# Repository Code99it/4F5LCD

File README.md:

# Installation und Nutzung  
# Installation and Usage  

**Dieses Projekt ersetzt bei Fahrzeugen der VAG-Gruppe mit Plattform 4F (C6) das kleine Display in der Mitte des Kombiinstruments durch eine spezielle Mikrocontroller-Lösung. Die Bedienung erfolgt über die linken Tasten am Lenkrad:**  
- Drehen am Rad wählt einen Listeneintrag.  
- Klicken auf das Drehrad aktiviert den gewählten Eintrag.  
- Die MODE-Taste am Lenkrad wechselt zwischen den Menüseiten.  
- Die Auf-Ab-Taste am Wischerhebel und die Bestätigungstaste auf der Hebel-Unterseite sind zunächst wirkungslos, die Funktion wird ggf. in späteren Projektversionen noch einmal aufgegriffen.

**This project replaces the small display in the center of the instrument cluster with a custom microcontroller solution for vehicles of the VAG group using platform 4F (C6). Operation is via the left steering wheel controls:**  
- Rotating the knob selects a list item.  
- Pressing the knob activates the selected item.  
- The MODE button on the steering wheel switches between menu pages.  
- The up/down button on the wiper stalk and the confirm button on the underside of the stalk are initially non-functional; this feature may be revisited in a future project version.

## Was dir dieses Projekt nützt  
## What This Project Does for You  

- Du erhältst schnellen, sicheren Zugriff auf fahrzeuginterne Statusdaten, um Temperatur-, Drehzahl- oder Komfortparameter zu überwachen.  
- You get fast, secure access to in-vehicle status data to monitor temperature, RPM, or comfort parameters.  

## 1. Systemzugriff einrichten  
## 1. Set Up System Access  

- Dieses System greift ausschließlich lesend auf die fahrzeuginternen Bussysteme (z. B. CAN-Bus) zu.  
- Es werden nur Statusinformationen wie Temperatur, Drehzahl oder Komfortdaten erfasst.  
- Kein Zugriff auf sicherheitskritische Systeme (Bremsen, Airbags, ESP, ABS, Antrieb).  
- Eine Beeinflussung, Veränderung oder Steuerung dieser Systeme ist weder vorgesehen noch implementiert.  

- No access to safety-critical systems (brakes, airbags, ESP, ABS, drivetrain).  
- Only status information such as temperature, RPM or comfort data is collected.  
- This system uses read-only access to the vehicle’s internal bus systems (e.g. CAN bus).  
- Any manipulation, alteration or control of these systems is neither intended nor implemented.  

## 2. Infotainment-Funktionen aktivieren  
## 2. Enable Infotainment Functions  

- Für Menüauswahl und Displayanzeige wird schreibender Zugriff auf nicht sicherheitsrelevante Steuergeräte verwendet.  
- Dieser Zugriff ist funktional begrenzt und beeinflusst weder Fahrverhalten noch Fahrsicherheit.  

- Write access to non-safety-critical control units is used for menu selection and display output.  
- This access is functionally limited and does not affect driving behavior or safety.  

## 3. CAN-Bus-Analyse durchführen  
## 3. Perform CAN-Bus Analysis  

- Sniffing im Rahmen des gesetzlich zulässigen Reverse Engineering (§ 69e UrhG) zur Interoperabilität.  
- Es wird keine Original-Software extrahiert, kopiert oder verändert – nur das Datenverhalten dokumentiert.  

- Sniffing under the legally permitted reverse engineering (§ 69e UrhG) for interoperability.  
- No original software is extracted, copied, or modified – only data behavior is documented.  

## 4. Nutzungshinweise  
## 4. Usage Notes  

- Du nutzt das System ausschließlich zu Test-, Entwicklungs- oder Forschungszwecken.  
- Dauerbetrieb im öffentlichen Straßenverkehr erfordert Einzelabnahme (§ 21 StVZO) bei TÜV/DEKRA etc.  

- Use exclusively for testing, development, or research purposes.  
- Permanent use on public roads requires single-vehicle approval (§ 21 StVZO) from TÜV/DEKRA, etc.  

## 5. Haftungsausschluss  
## 5. Disclaimer  

- Nicht autorisiert, geprüft oder freigegeben durch einen Fahrzeughersteller; keine offizielle Verbindung zu Herstellern der VAG-Gruppe.  
- Jegliche Nutzung erfolgt auf eigene Verantwortung.  

- Not authorized, tested, or approved by any vehicle manufacturer; no official affiliation with any brand of the VAG group.  
- Any use is at your own risk.

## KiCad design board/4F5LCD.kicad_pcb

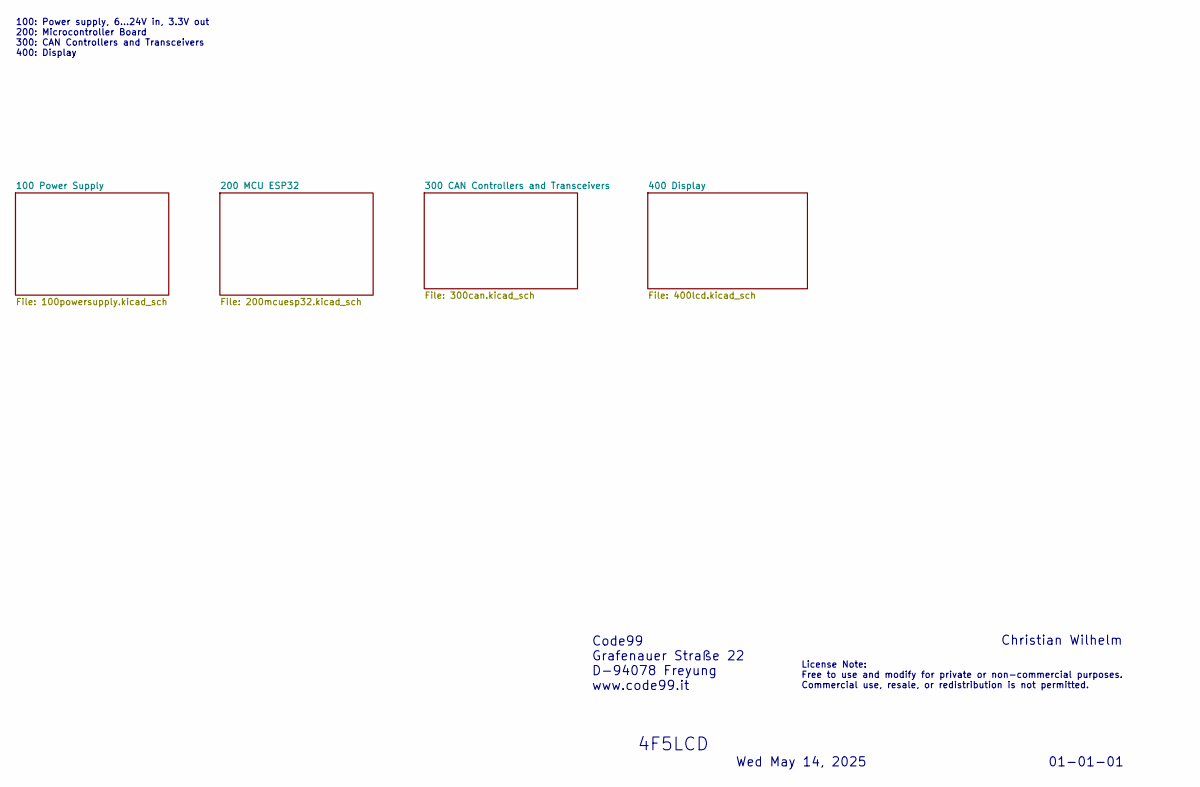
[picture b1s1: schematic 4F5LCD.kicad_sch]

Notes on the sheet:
Wed May 14, 2025
Code99 Grafenauer Straße 22 D-94078 Freyung www.code99.it
4F5LCD
100: Power supply, 6...24V in, 3.3V out 200: Microcontroller Board 300: CAN Controllers and Transceivers 400: Display
01-01-01
Christian Wilhelm
License Note: Free to use and modify for private or non-commercial purposes. Commercial use, resale, or redistribution is not permitted.

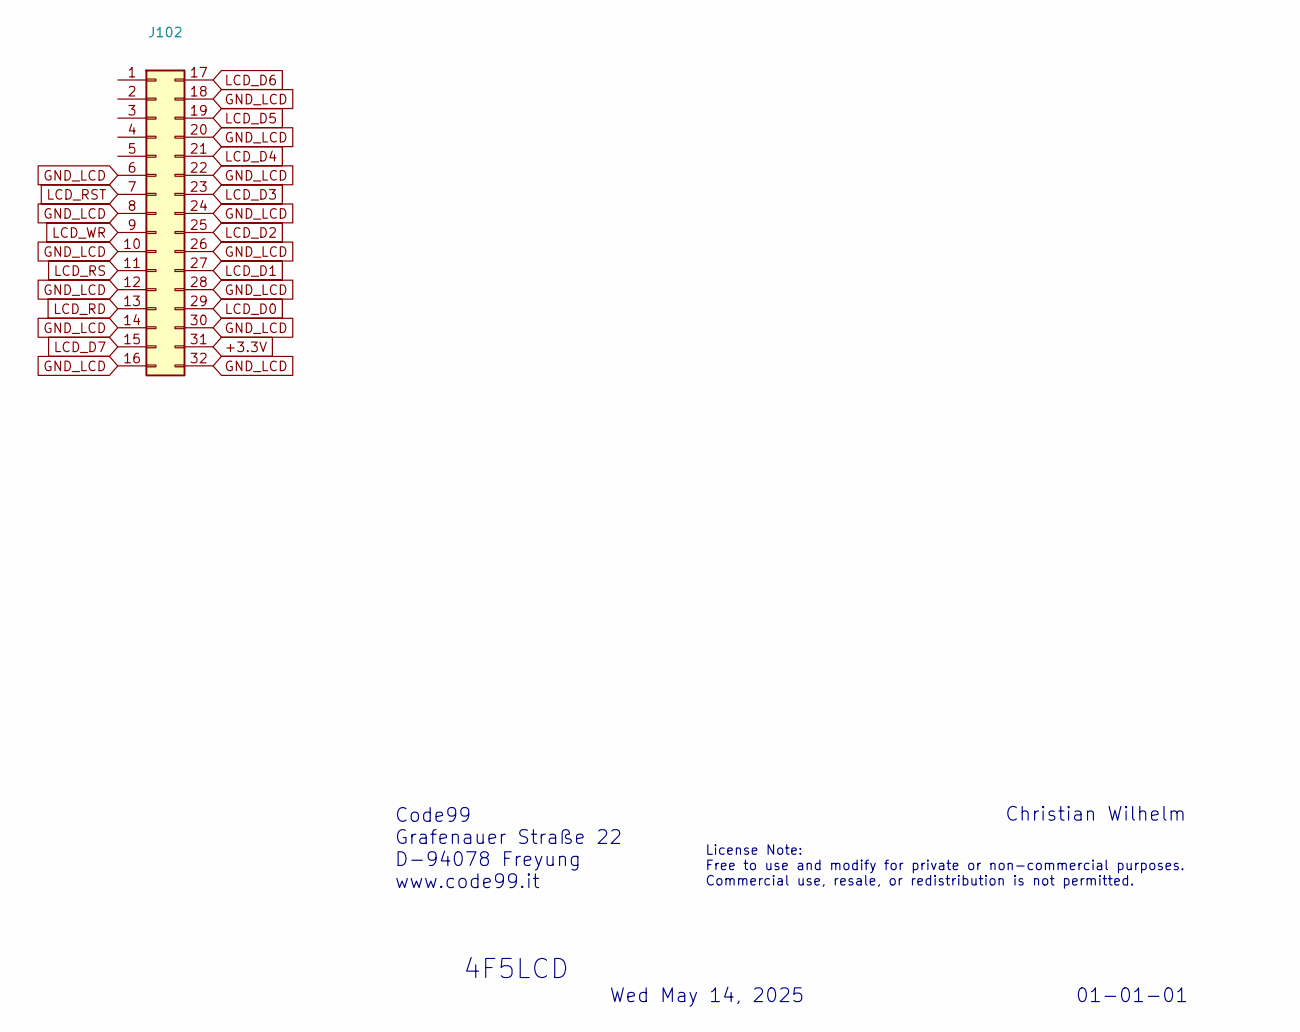
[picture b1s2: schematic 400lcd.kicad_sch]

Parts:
J102: Conn_02x16_Top_Bottom; PinHeader_2x16_P2.54mm_Horizontal

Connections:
+3.3V: J102.31; also elsewhere on the board
GND_LCD: J102.6, J102.8, J102.10, J102.12, J102.14, J102.16, J102.18, J102.20, J102.22, J102.24, J102.26, J102.28, J102.30, J102.32
LCD_D0: J102.29; also elsewhere on the board
LCD_D1: J102.27; also elsewhere on the board
LCD_D2: J102.25; also elsewhere on the board
LCD_D3: J102.23; also elsewhere on the board
LCD_D4: J102.21; also elsewhere on the board
LCD_D5: J102.19; also elsewhere on the board
LCD_D6: J102.17; also elsewhere on the board
LCD_D7: J102.15; also elsewhere on the board
LCD_RD: J102.13; also elsewhere on the board
LCD_RS: J102.11; also elsewhere on the board
LCD_WR: J102.9; also elsewhere on the board

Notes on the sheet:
License Note: Free to use and modify for private or non-commercial purposes. Commercial use, resale, or redistribution is not permitted.
01-01-01
Code99 Grafenauer Straße 22 D-94078 Freyung www.code99.it
4F5LCD
Christian Wilhelm
Wed May 14, 2025

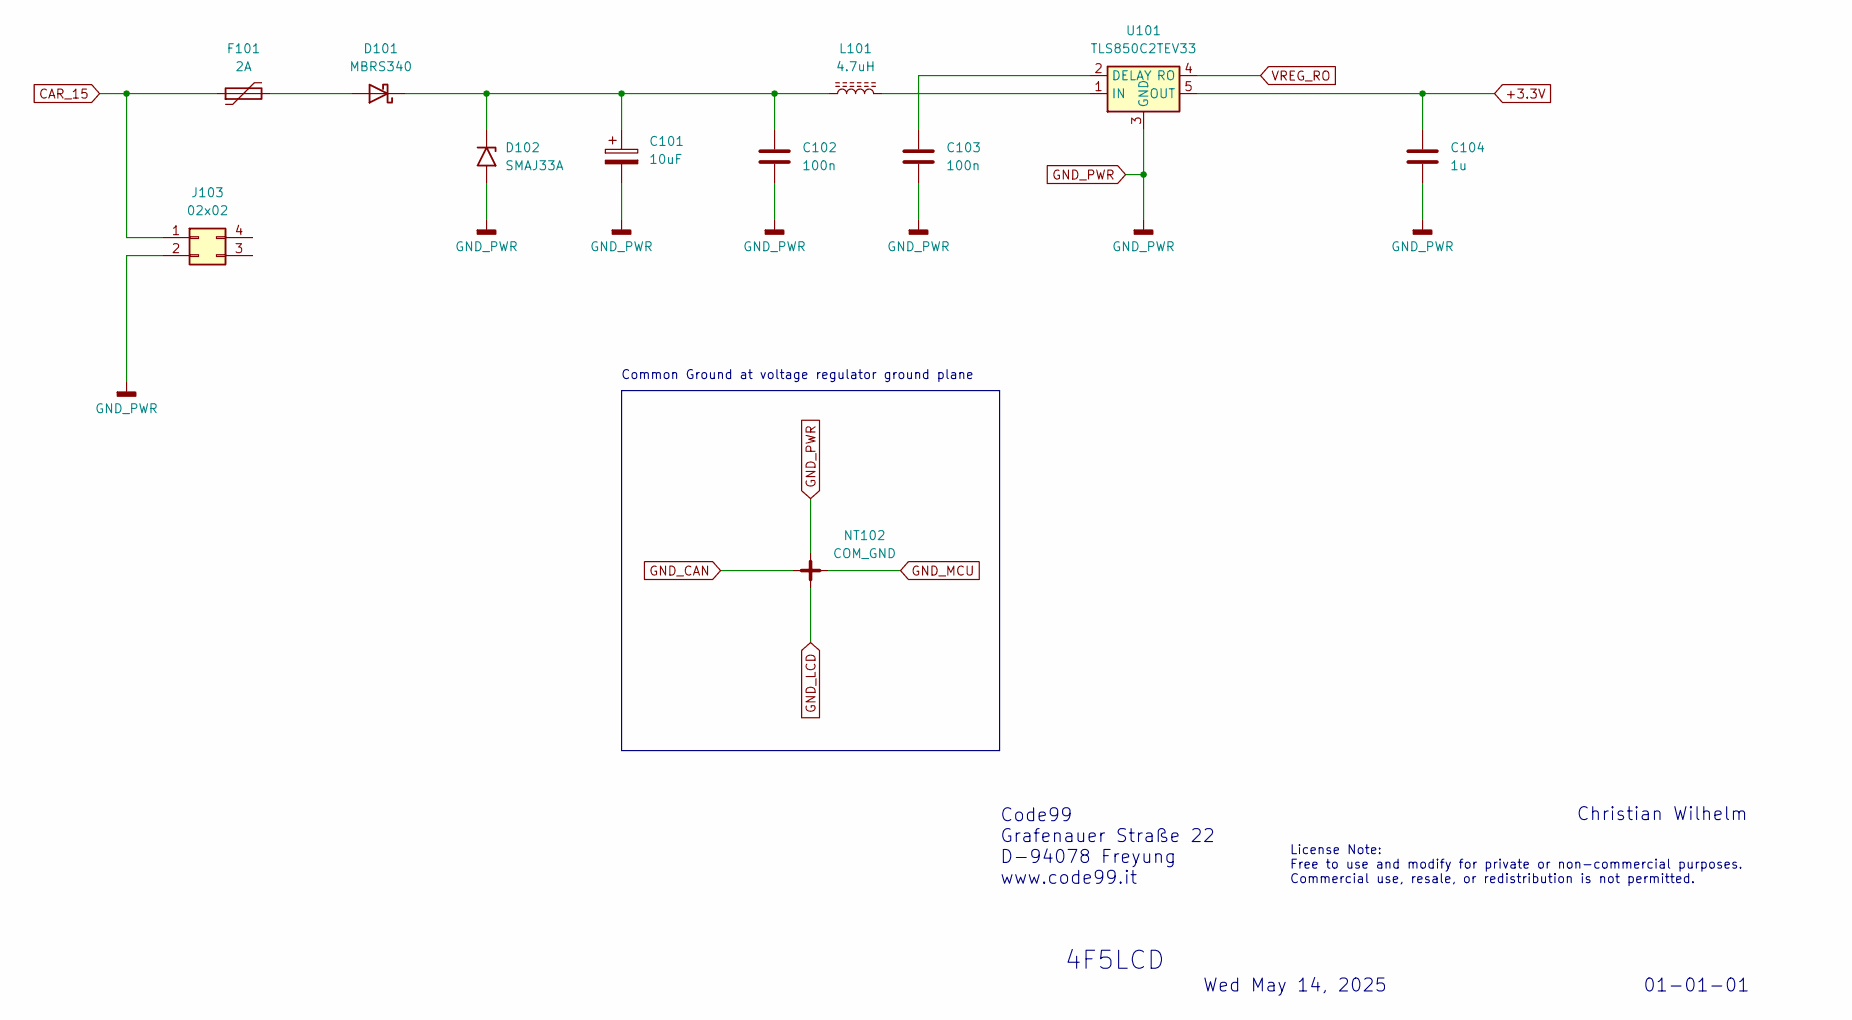
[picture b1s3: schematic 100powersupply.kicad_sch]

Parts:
C101: 10uF; CP_Elec_5x5.9
C102, C103: 100n; C_1206_3216Metric_Pad1.33x1.80mm_HandSolder
C104: 1u; C_1206_3216Metric_Pad1.33x1.80mm_HandSolder
D101: MBRS340; D_SMC
D102: SMAJ33A; D_SMA
F101: 2A; Fuse_Bourns_MF-SM_7.98x5.44mm
J103: 02x02; PinHeader_2x02_P2.54mm_Horizontal
L101: 4.7uH; L_Ferrocore_DLG-0403
NT102: COM_GND
U101: TLS850C2TEV33; TO-252-4

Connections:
+3.3V: C104.1, U101.5 (OUT); also elsewhere on the board
CAR_15: F101.1, J103.1
GND_PWR: C101.2, C102.2, C103.2, C104.2, D102.2 (A2), J103.2, NT102.3, U101.3 (GND)
unnamed: D101.2 (A), F101.2
unnamed: C101.1, C102.1, D101.1 (K), D102.1 (A1), L101.1
unnamed: C103.1, U101.2 (DELAY)
unnamed: L101.2, U101.1 (IN)
VREG_RO: U101.4 (RO); also elsewhere on the board

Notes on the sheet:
Wed May 14, 2025
Code99 Grafenauer Straße 22 D-94078 Freyung www.code99.it
License Note: Free to use and modify for private or non-commercial purposes. Commercial use, resale, or redistribution is not permitted.
4F5LCD
01-01-01
Common Ground at voltage regulator ground plane
Christian Wilhelm

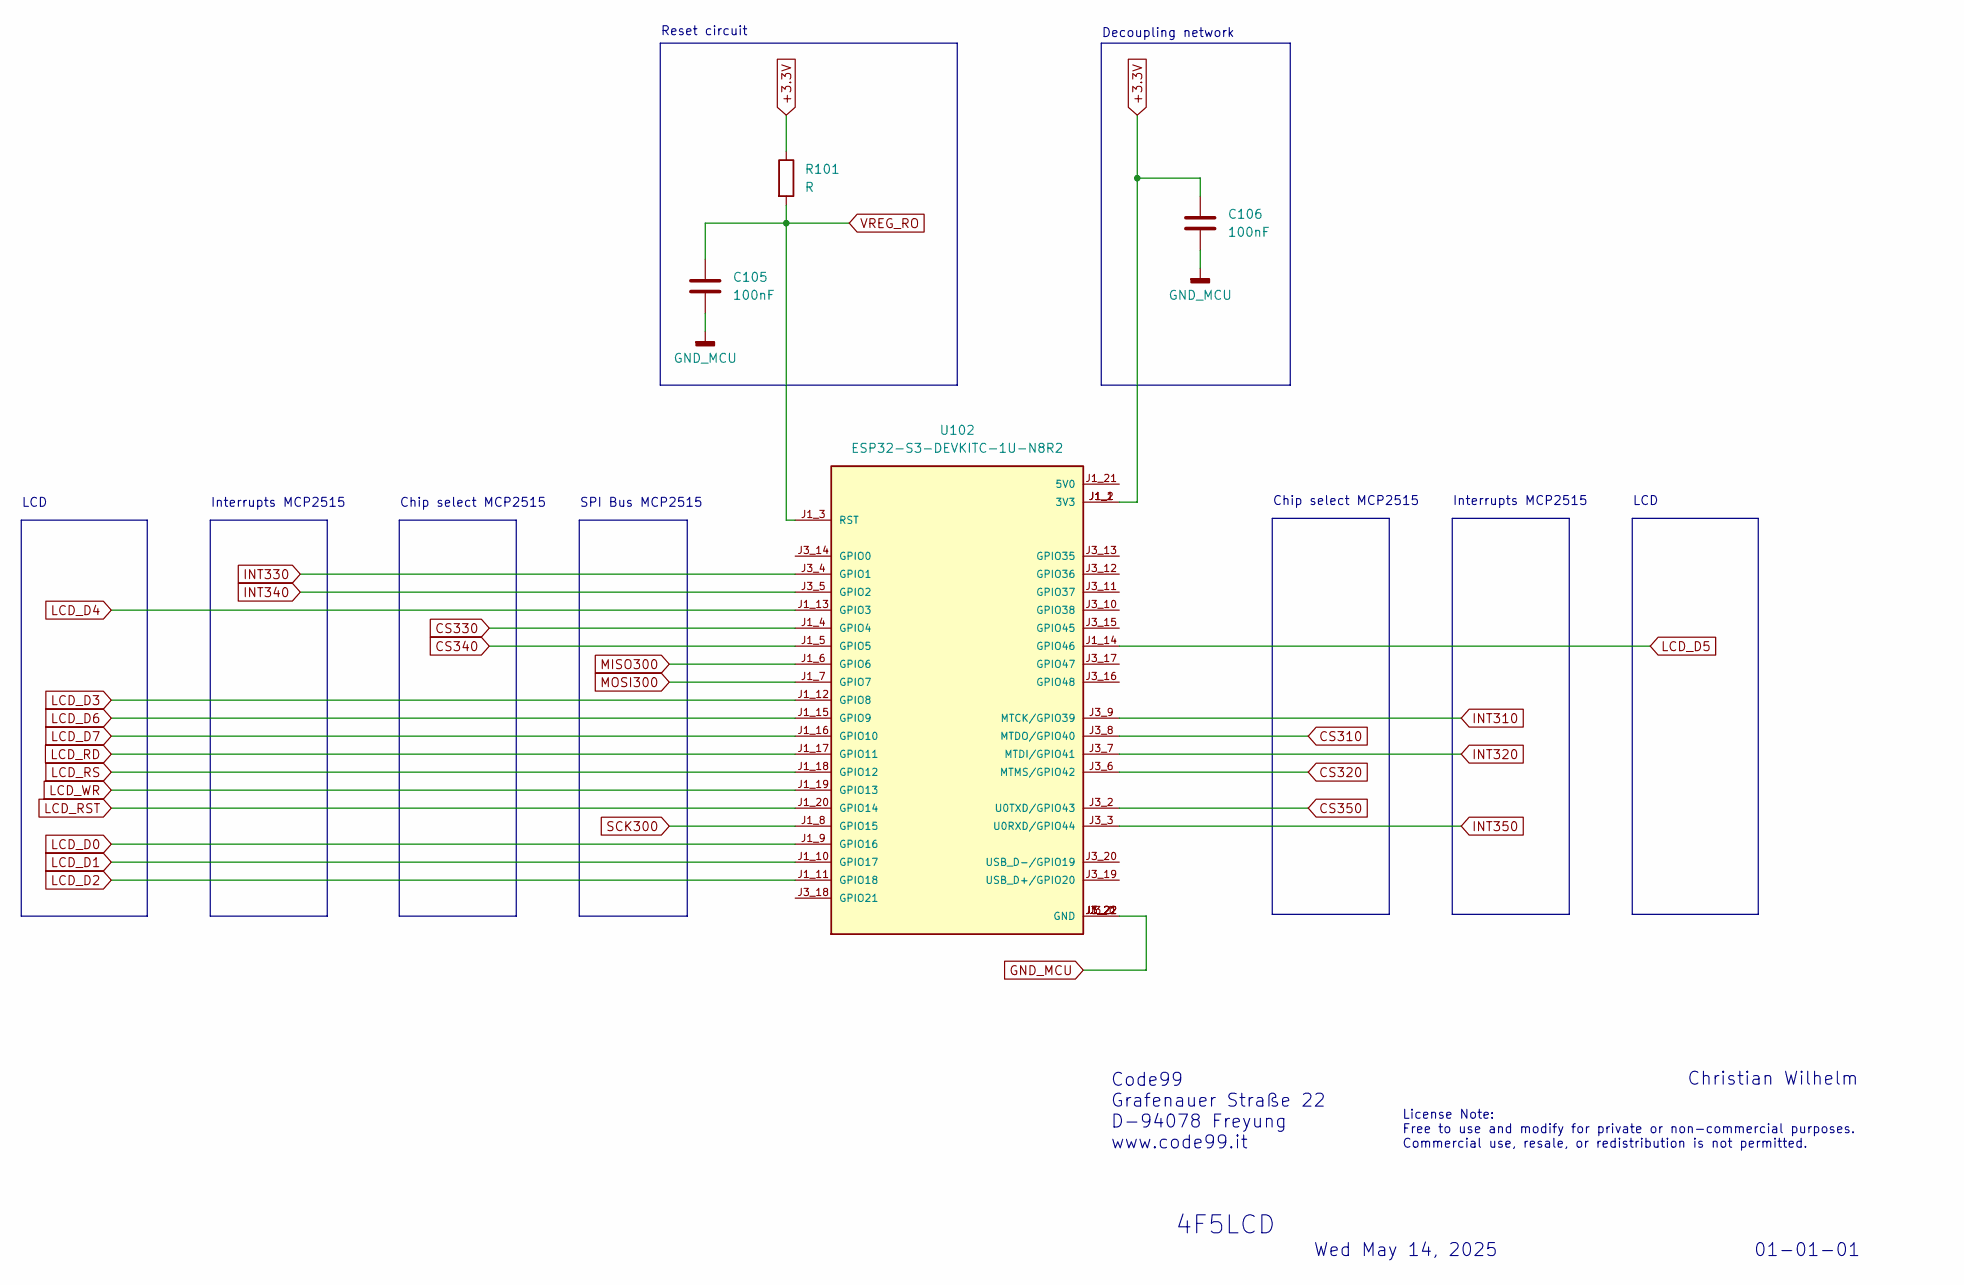
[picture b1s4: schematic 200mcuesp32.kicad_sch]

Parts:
C105: 100nF
C106: 100nF; C_1206_3216Metric_Pad1.33x1.80mm_HandSolder
R101: R
U102: ESP32-S3-DEVKITC-1U-N8R2; XCVR_ESP32-S3-DEVKITC-1U-N8R2; PARTREV 5.3

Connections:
+3.3V: C106.1, R101.1, U102.J1_1 (3V3), U102.J1_2 (3V3); also elsewhere on the board
CS310: U102.J3_8 (MTDO/GPIO40); also elsewhere on the board
CS320: U102.J3_6 (MTMS/GPIO42); also elsewhere on the board
CS330: U102.J1_4 (GPIO4); also elsewhere on the board
CS340: U102.J1_5 (GPIO5); also elsewhere on the board
CS350: U102.J3_2 (U0TXD/GPIO43); also elsewhere on the board
GND_MCU: C105.2, C106.2, U102.J1_22 (GND), U102.J3_1 (GND), U102.J3_21 (GND), U102.J3_22 (GND); also elsewhere on the board
INT310: U102.J3_9 (MTCK/GPIO39); also elsewhere on the board
INT320: U102.J3_7 (MTDI/GPIO41); also elsewhere on the board
INT330: U102.J3_4 (GPIO1); also elsewhere on the board
INT340: U102.J3_5 (GPIO2); also elsewhere on the board
INT350: U102.J3_3 (U0RXD/GPIO44); also elsewhere on the board
LCD_D0: U102.J1_9 (GPIO16); also elsewhere on the board
LCD_D1: U102.J1_10 (GPIO17); also elsewhere on the board
LCD_D2: U102.J1_11 (GPIO18); also elsewhere on the board
LCD_D3: U102.J1_12 (GPIO8); also elsewhere on the board
LCD_D4: U102.J1_13 (GPIO3); also elsewhere on the board
LCD_D5: U102.J1_14 (GPIO46); also elsewhere on the board
LCD_D6: U102.J1_15 (GPIO9); also elsewhere on the board
LCD_D7: U102.J1_16 (GPIO10); also elsewhere on the board
LCD_RD: U102.J1_17 (GPIO11); also elsewhere on the board
LCD_RS: U102.J1_18 (GPIO12); also elsewhere on the board
LCD_WR: U102.J1_19 (GPIO13); also elsewhere on the board
MISO300: U102.J1_6 (GPIO6); also elsewhere on the board
MOSI300: U102.J1_7 (GPIO7); also elsewhere on the board
SCK300: U102.J1_8 (GPIO15); also elsewhere on the board
VREG_RO: C105.1, R101.2, U102.J1_3 (RST); also elsewhere on the board

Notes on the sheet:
License Note: Free to use and modify for private or non-commercial purposes. Commercial use, resale, or redistribution is not permitted.
LCD
01-01-01
Reset circuit
Chip select MCP2515
Interrupts MCP2515
Code99 Grafenauer Straße 22 D-94078 Freyung www.code99.it
Decoupling network
4F5LCD
SPI Bus MCP2515
Christian Wilhelm
Wed May 14, 2025

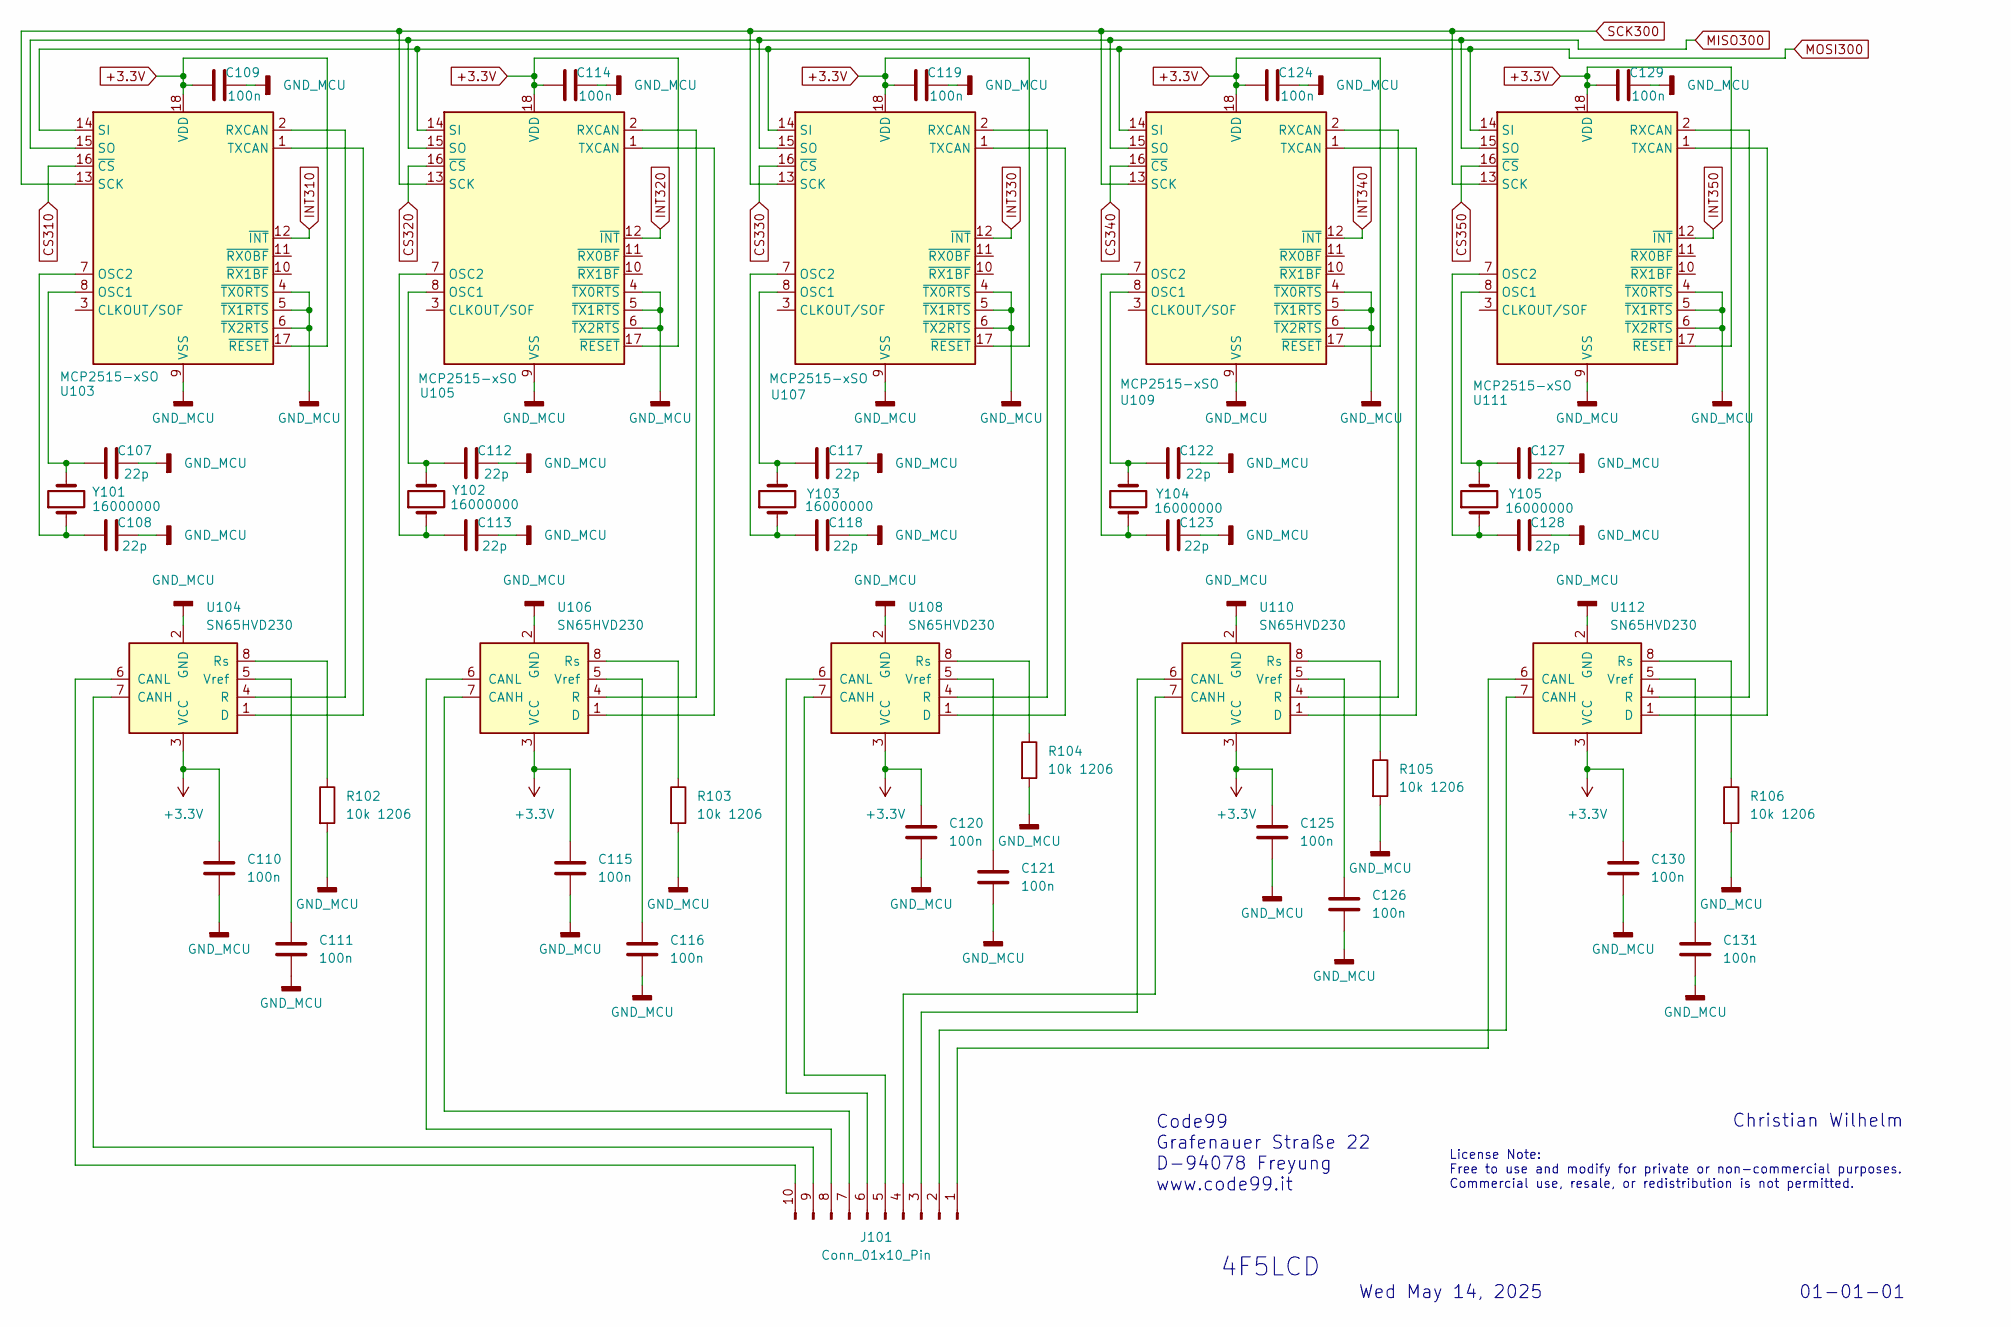
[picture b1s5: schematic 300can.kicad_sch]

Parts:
C107, C108, C112, C113, C117, C118, C122, C123, C127, C128: 22p; C_0603_1608Metric
C109, C110, C111, C114, C115, C116, C119, C120, C121, C124, C125, C126, C129, C130, C131: 100n; C_1206_3216Metric
J101: Conn_01x10_Pin; IDC-Header_2x05_P2.54mm_Horizontal
R102, R103, R104, R105, R106: 10k 1206; R_1206_3216Metric
U103, U105, U107, U109, U111: MCP2515-xSO; SOIC-18W_7.5x11.6mm_P1.27mm
U104, U106, U108, U110, U112: SN65HVD230; SOIC-8_3.9x4.9mm_P1.27mm
Y101, Y102, Y103, Y104, Y105: 16000000; Crystal_SMD_Abracon_ABM3-2Pin_5.0x3.2mm

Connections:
+3.3V: C109.1, C110.1, C114.1, C115.1, C119.1, C120.1, C124.1, C125.1, C129.1, C130.1, U103.17 (~RESET), U103.18 (VDD), U104.3 (VCC), U105.17 (~RESET), U105.18 (VDD), U106.3 (VCC), U107.17 (~RESET), U107.18 (VDD), U108.3 (VCC), U109.17 (~RESET), U109.18 (VDD), U110.3 (VCC), U111.17 (~RESET), U111.18 (VDD), U112.3 (VCC); also elsewhere on the board
CS310: U103.16 (~CS); also elsewhere on the board
CS320: U105.16 (~CS); also elsewhere on the board
CS330: U107.16 (~CS); also elsewhere on the board
CS340: U109.16 (~CS); also elsewhere on the board
CS350: U111.16 (~CS); also elsewhere on the board
GND_MCU: C107.2, C108.1, C109.2, C110.2, C111.2, C112.2, C113.1, C114.2, C115.2, C116.2, C117.2, C118.1, C119.2, C120.2, C121.2, C122.2, C123.1, C124.2, C125.2, C126.2, C127.2, C128.1, C129.2, C130.2, C131.2, R102.2, R103.2, R104.2, R105.2, R106.2, U103.4 (~TX0RTS), U103.5 (~TX1RTS), U103.6 (~TX2RTS), U103.9 (VSS), U104.2 (GND), U105.4 (~TX0RTS), U105.5 (~TX1RTS), U105.6 (~TX2RTS), U105.9 (VSS), U106.2 (GND), U107.4 (~TX0RTS), U107.5 (~TX1RTS), U107.6 (~TX2RTS), U107.9 (VSS), U108.2 (GND), U109.4 (~TX0RTS), U109.5 (~TX1RTS), U109.6 (~TX2RTS), U109.9 (VSS), U110.2 (GND), U111.4 (~TX0RTS), U111.5 (~TX1RTS), U111.6 (~TX2RTS), U111.9 (VSS), U112.2 (GND); also elsewhere on the board
INT310: U103.12 (~INT); also elsewhere on the board
INT320: U105.12 (~INT); also elsewhere on the board
INT330: U107.12 (~INT); also elsewhere on the board
INT340: U109.12 (~INT); also elsewhere on the board
INT350: U111.12 (~INT); also elsewhere on the board
MISO300: U103.15 (SO), U105.15 (SO), U107.15 (SO), U109.15 (SO), U111.15 (SO); also elsewhere on the board
MOSI300: U103.14 (SI), U105.14 (SI), U107.14 (SI), U109.14 (SI), U111.14 (SI); also elsewhere on the board
unnamed: J101.1, U112.6 (CANL)
unnamed: J101.2, U112.7 (CANH)
unnamed: J101.3, U110.6 (CANL)
unnamed: J101.4, U110.7 (CANH)
unnamed: J101.5, U108.7 (CANH)
unnamed: J101.6, U108.6 (CANL)
unnamed: J101.7, U106.7 (CANH)
unnamed: J101.8, U106.6 (CANL)
unnamed: J101.9, U104.7 (CANH)
unnamed: J101.10, U104.6 (CANL)
unnamed: C107.1, U103.8 (OSC1), Y101.2
unnamed: C108.2, U103.7 (OSC2), Y101.1
unnamed: U103.2 (RXCAN), U104.4 (R)
unnamed: U103.1 (TXCAN), U104.1 (D)
unnamed: R102.1, U104.8 (Rs)
unnamed: C111.1, U104.5 (Vref)
unnamed: C112.1, U105.8 (OSC1), Y102.2
unnamed: C113.2, U105.7 (OSC2), Y102.1
unnamed: U105.2 (RXCAN), U106.4 (R)
unnamed: U105.1 (TXCAN), U106.1 (D)
unnamed: R103.1, U106.8 (Rs)
unnamed: C116.1, U106.5 (Vref)
unnamed: C117.1, U107.8 (OSC1), Y103.2
unnamed: C118.2, U107.7 (OSC2), Y103.1
unnamed: U107.2 (RXCAN), U108.4 (R)
unnamed: U107.1 (TXCAN), U108.1 (D)
unnamed: R104.1, U108.8 (Rs)
unnamed: C121.1, U108.5 (Vref)
unnamed: C122.1, U109.8 (OSC1), Y104.2
unnamed: C123.2, U109.7 (OSC2), Y104.1
unnamed: U109.2 (RXCAN), U110.4 (R)
unnamed: U109.1 (TXCAN), U110.1 (D)
unnamed: R105.1, U110.8 (Rs)
unnamed: C126.1, U110.5 (Vref)
unnamed: C127.1, U111.8 (OSC1), Y105.2
unnamed: C128.2, U111.7 (OSC2), Y105.1
unnamed: U111.2 (RXCAN), U112.4 (R)
unnamed: U111.1 (TXCAN), U112.1 (D)
unnamed: R106.1, U112.8 (Rs)
unnamed: C131.1, U112.5 (Vref)
SCK300: U103.13 (SCK), U105.13 (SCK), U107.13 (SCK), U109.13 (SCK), U111.13 (SCK); also elsewhere on the board

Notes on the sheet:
Wed May 14, 2025
License Note: Free to use and modify for private or non-commercial purposes. Commercial use, resale, or redistribution is not permitted.
Code99 Grafenauer Straße 22 D-94078 Freyung www.code99.it
4F5LCD
Christian Wilhelm
01-01-01

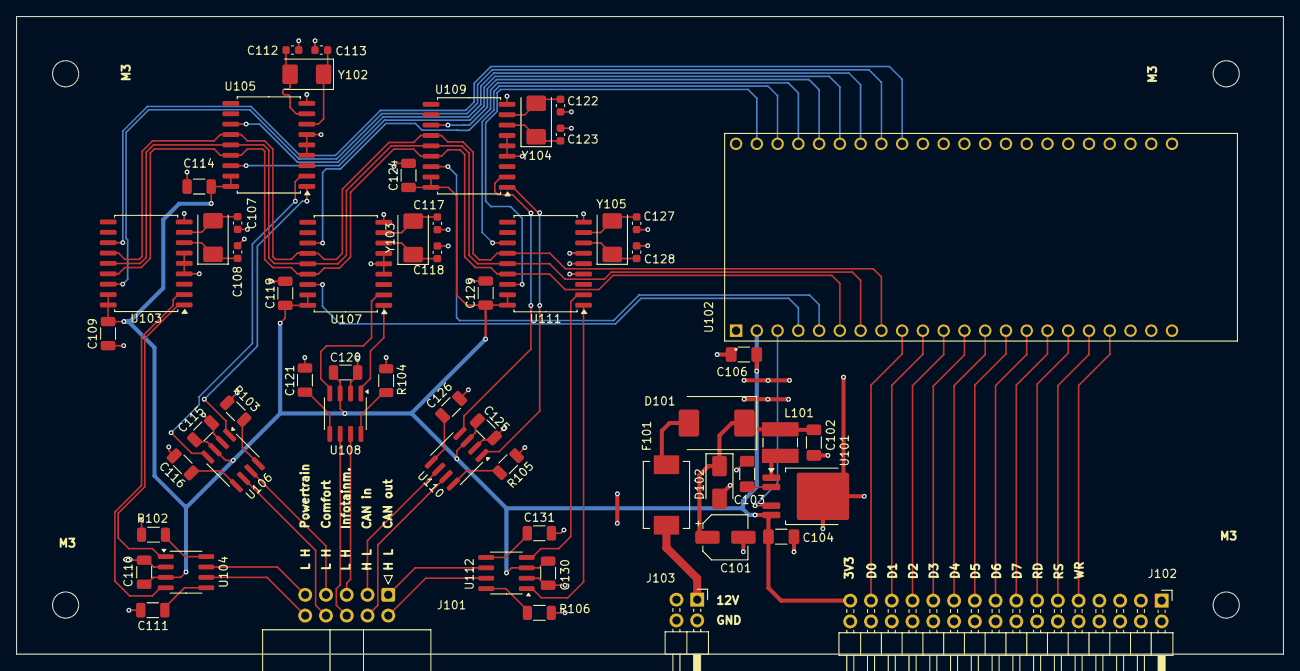
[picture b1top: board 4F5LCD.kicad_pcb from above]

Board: 2 copper layers, 155.0 x 78.0 mm, 59 parts (0 on the bottom side), 74 nets.

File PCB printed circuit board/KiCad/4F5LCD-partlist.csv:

"Id";"Designator";"Footprint";"Quantity";"Designation";"Supplier and ref";
1;"J103";"PhoenixContact_MC_1,5_2-G-3.81_1x02_P3.81mm_Horizontal";1;"02x02";;;
2;"J102";"IDC-Header_2x13-1MP_P2.54mm_Latch_Horizontal";1;"Conn_02x16_Top_Bottom";;;
3;"J101";"AMPHENOL_10153118-116KALF";1;"Conn_01x10_Pin";;;
4;"U112,U104,U110,U108,U106";"SOIC-8_3.9x4.9mm_P1.27mm";5;"SN65HVD230";;;
5;"C130,C109,C121,C126,C115,C124,C114,C119,C111,C116,C129,C110,C125,C131,C120";"C_1206_3216Metric";15;"100n";;;
6;"R106,R103,R104,R105,R102";"R_1206_3216Metric";5;"10k 1206";;;
7;"C108,C128,C107,C117,C122,C112,C127,C123,C118,C113";"C_0603_1608Metric";10;"22p";;;
8;"Y103,Y105,Y101,Y104,Y102";"Crystal_SMD_Abracon_ABM3-2Pin_5.0x3.2mm";5;"16000000";;;
9;"U107,U109,U105,U111,U103";"SOIC-18W_7.5x11.6mm_P1.27mm";5;"MCP2515-xSO";;;
10;"C102,C103";"C_1206_3216Metric_Pad1.33x1.80mm_HandSolder";2;"100n";;;
11;"U101";"TO-252-4";1;"TLS850C2TEV33";;;
12;"U102";"XCVR_ESP32-S3-DEVKITC-1U-N8R2";1;"ESP32-S3-DEVKITC-1U-N8R2";;;
13;"F101";"Fuse_Bourns_MF-SM_7.98x5.44mm";1;"2A";;;
14;"D101";"D_SMC";1;"MBRS340";;;
15;"C104";"C_1206_3216Metric_Pad1.33x1.80mm_HandSolder";1;"1u";;;
16;"C106";"C_1206_3216Metric_Pad1.33x1.80mm_HandSolder";1;"100nF";;;
17;"C101";"CP_Elec_5x5.9";1;"10uF";;;
18;"L101";"L_Ferrocore_DLG-0403";1;"4.7uH";;;
19;"D102";"D_SMA";1;"SMAJ33A";;;

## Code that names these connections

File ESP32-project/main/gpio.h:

/**
 * @file gpio.h
 * 
 * @brief GPIO pin definitions for 8-bit parallel LCD interface (ESP32-S3)
 * 
 * @author Christian Wilhelm (cw1@code99.it)
 * @version 1.0.1
 * @date 2025-06-02
 *
 * This file defines the GPIO mappings for data and control signals
 * used to connect an 8-bit parallel LCD to the ESP32-S3. All selected
 * pins are safe to use — they are not reserved for flash, USB, or
 * bootstrapping, and are fully output-capable.
 * 
 */

#ifndef GPIO_H
#define GPIO_H

#include <stdint.h>
#include "driver/gpio.h"

// LCD Data wires (should be in a continous row)
#define LCD_DATA_0 GPIO_NUM_35
#define LCD_DATA_1 GPIO_NUM_36
#define LCD_DATA_2 GPIO_NUM_37
#define LCD_DATA_3 GPIO_NUM_38
#define LCD_DATA_4 GPIO_NUM_39
#define LCD_DATA_5 GPIO_NUM_40
#define LCD_DATA_6 GPIO_NUM_41
#define LCD_DATA_7 GPIO_NUM_42

// LCD Command wires
#define LCD_RD   GPIO_NUM_14   
#define LCD_WR   GPIO_NUM_15
#define LCD_RS   GPIO_NUM_16   
#define LCD_CS   GPIO_NUM_17  
#define LCD_RST  GPIO_NUM_18

#define HIGH true
#define LOW false

#endif

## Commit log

2025-05-08 Grundlegende Dateien hinzugefügt
2025-05-08 Installationsanleitung hinzugefügt
2025-05-08 Add English installation guide (install_en_US.md)
2025-05-08 Added flash instructions
2025-05-08 Added a simple READY. output to main.c who is visible in monitor in console
2025-05-08 Added some basic functions for reading can messages
2025-05-08 Für alle Dateien ausführliche Codekommentare hinzugefügt. Added extended code comments for all files.
2025-05-08 Ordner dev/ und Projektdatei für Sublime Text hinzugefügt. Added dev/ and project file for sublime text.
2025-05-09 Removed trademarked brand names for legal compliance, added Legal.md
2025-05-09 Added PNG file containing display previews
2025-05-13 Added additional schematic for LCD
2025-05-13 Added Schematic screenshots
2025-05-14 Added stl and skp files for 3D printing, changed ground planes and net names, exported schematics as pdf
2025-06-01 Refactored project structure, added missing files, and created required folders.
2025-06-02 wrote entire esp32 project new, created new c and h files, improved LCD FPS from 1 to 6.8
2025-06-02 added some c functions to fill lcd with letters and color test functions
2025-06-02 added some test values and improved display speed
2025-06-04 added a menu selector icon like the one in the OEM LCD
2025-06-04 improvements and changes in menu bar
2025-06-07 added folder with fotos from speedometer and lcd
2025-06-07 Photos: Solution with a 3D-printed mounting frame for the LCD
2025-06-07 changed and added display drivers
2025-06-08 added electrical pinout for wiper stalk
2025-06-08 added wiring diagram for left steering wheel buttons
